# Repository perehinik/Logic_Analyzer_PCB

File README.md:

# Logic_Analizer_PCB
KiCad PCB project of Logic Analyzer

All components were soldered by hand using Zhaoxin 898DH station

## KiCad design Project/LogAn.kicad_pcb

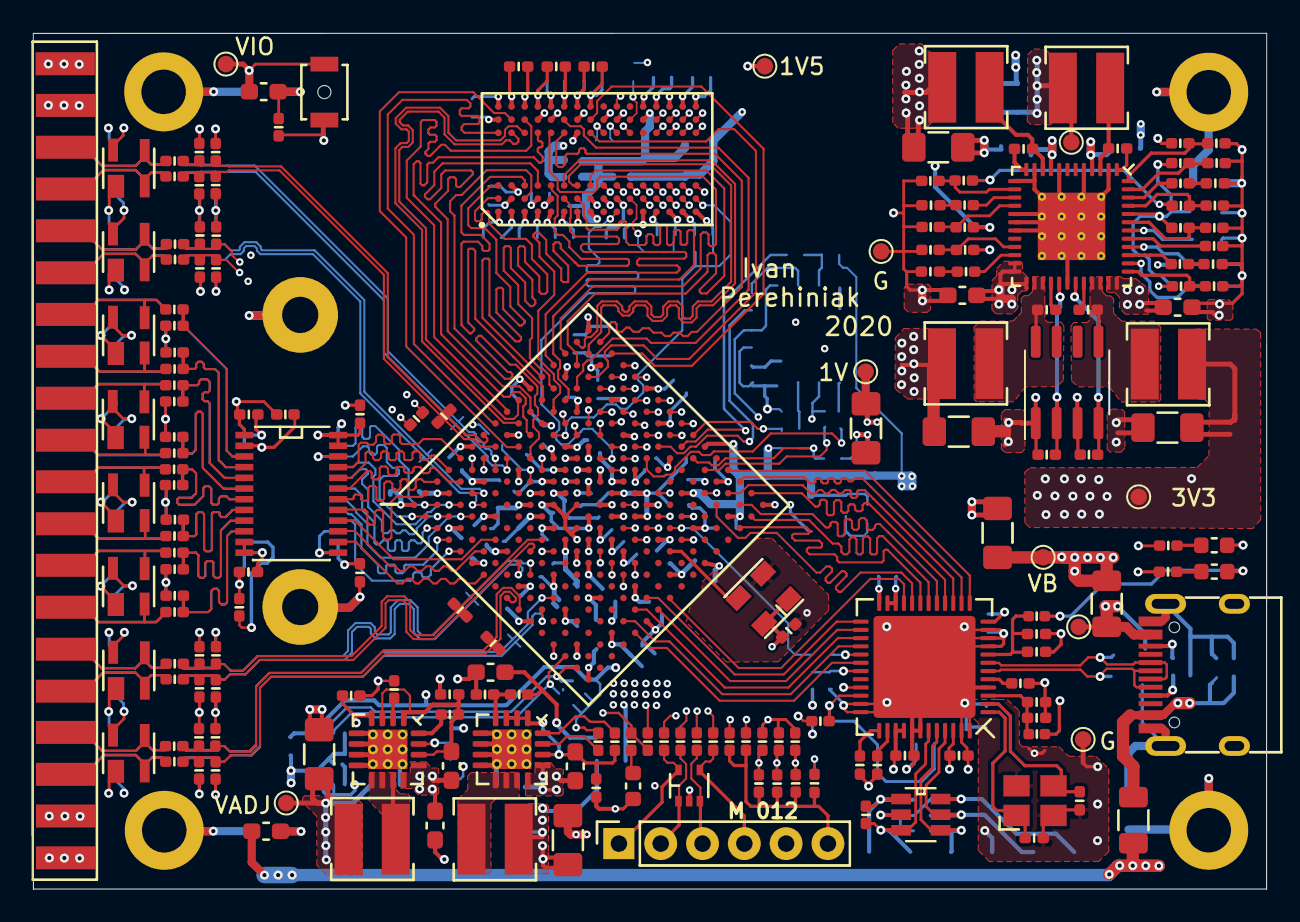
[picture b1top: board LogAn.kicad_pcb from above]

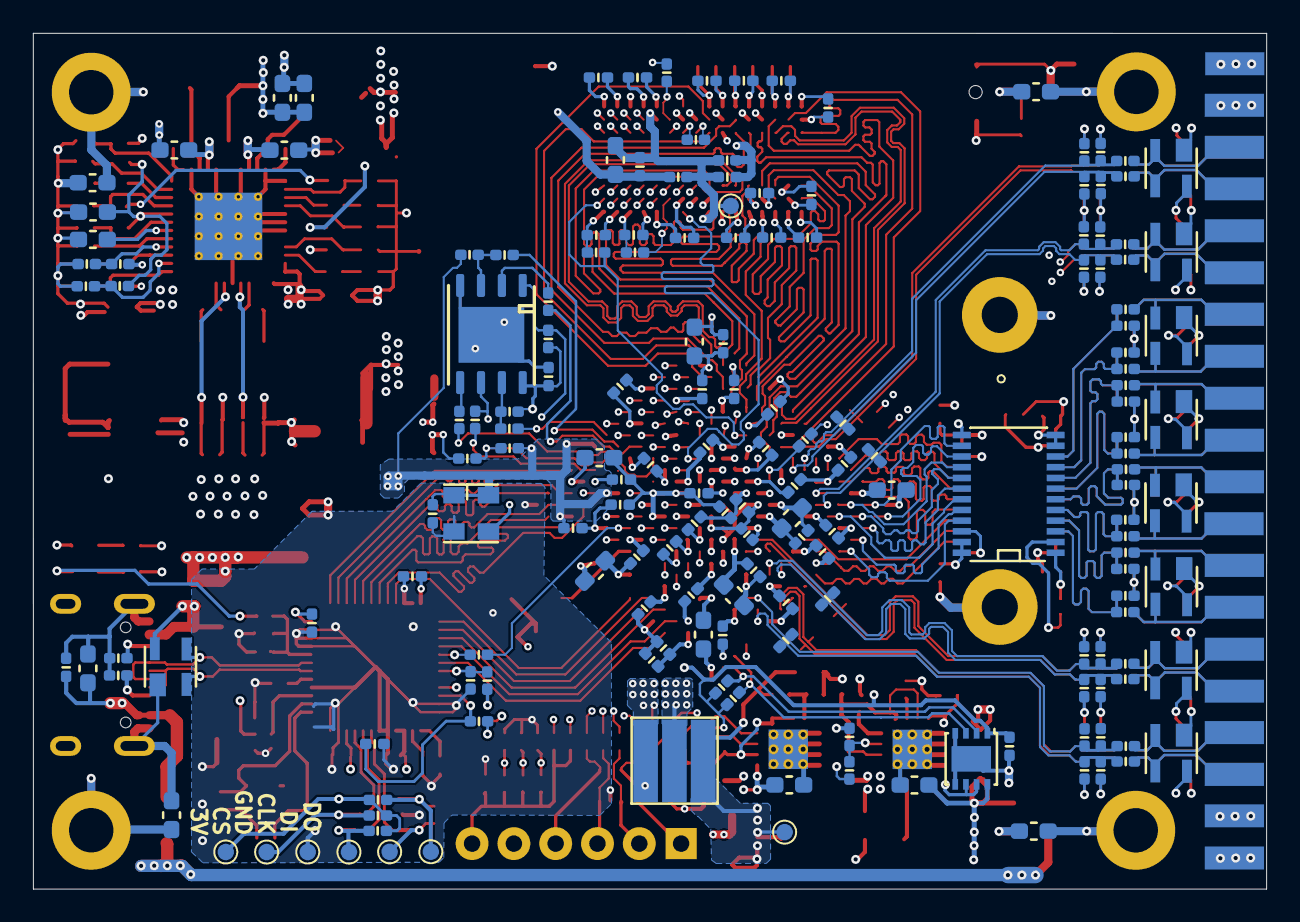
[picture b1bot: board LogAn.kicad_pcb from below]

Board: 6 copper layers, 74.9 x 52.0 mm, 366 parts (174 on the bottom side), 264 nets.

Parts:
C101, C525, C807, C808, C824, C825, C827: C_100u_1206_6V3; C_1206_3216Metric_Pad1.42x1.75mm_HandSolder
C102, C201, C401, C402, C403, C404, C521, C534, C601, C605, C606, C607, C608, C610, C611, C612, C802, C804, C809, C820, C821, C822, C823: C_100n_0402_16V; C_0402_1005Metric
C103, C503, C511, C516, C518, C535, C537, C801, C803, C805, C806: C_47u_0603_6V3; C_0603_1608Metric_Pad1.05x0.95mm_HandSolder
C104, C105, C810, C811, C812, C813: C_10u_0603_10V; C_0603_1608Metric_Pad1.05x0.95mm_HandSolder
C301, C302, C303, C304, C305, C306, C307, C308, C309, C310, C311, C312, C313, C314, C315, C316, C317: C_47n_0402_16V; C_0402_1005Metric
C318, C814, C819: C_1u_0603_10V; C_0603_1608Metric_Pad1.05x0.95mm_HandSolder
C319, C320, C506, C604, C701, C702: C_10n_0402_16V; C_0402_1005Metric
C501, C502, C505, C507, C509, C517, C519, C520, C522, C523, C524, C526, C527, C529: C_470n_0402_6V3; C_0402_1005Metric
C504, C508, C510, C512, C513, C515, C528, C530, C531, C532, C533, C536, C609, C613: C_4u7_0402_6V3; C_0402_1005Metric
C514: C_470n_0603_16V; C_0603_1608Metric_Pad1.05x0.95mm_HandSolder
C602, C603: C_27p_0402_16V; C_0402_1005Metric
C815: C_2n7_0402_10V; C_0402_1005Metric
C816: C_5n6_0402_10V; C_0402_1005Metric
C817, C818: C_1n8_0402_10V; C_0402_1005Metric
C826, C828: C_22u_0603_6V3; C_0603_1608Metric_Pad1.05x0.95mm_HandSolder
D201: D_NSQA6V8AW5T2_SOT23; SOT-353_SC-70-5
F101, F102: F_Polyfuse_1A_1206; Fuse_1206_3216Metric
FB501, FB502, FB601, FB602: FB_600R_100MHz_0,5A; L_0402_1005Metric
IC101, IC403, IC404, IC405, IC406, IC407, IC408, IC409, IC410, IC411, IC412, IC413, IC414, IC415, IC416, IC417, IC418: IC_TPD2E001DZD; SOT-143(R_PDSO-G4)
IC201: IC_XC7A15T_FTG256; Xilinx_FTG256
IC202: IC_S25FL064L-ABNFI040_WSON8; WSON-8-1EP_6x5mm_P1.27mm_EP3.4x4mmj
IC301: IC_MT41K128M16JT-125K_FBGA96; FBGA96_C80P9X16_800X1400X120
IC401, IC402: IC_SN74AVC8T245PW_TSSOP_24; TSSOP-24_4.4x7.8mm_P0.65mm
IC601: IC_93LC56BT-1OT; SOT-23-6
IC602: IC_FT232H_QFN48; QFN-48-1EP_8x8mm_P0.5mm_EP6.2x6.2mm
IC701, IC702: IC_ASEM1_100MHZ_3.2_2.5; OSC_SMD_3225-4Pin_3.2x2.5mm
IC801, IC802: IC_ADP2164; LFCSP-16-1EP_4x4mm_P0.65mm_EP2.4x2.4mm_ThermalVias
IC803: IC_MAX5417; DFN-8-1EP_3x3mm_P0.65mm_EP1.55x2.4mm
IC804: IC_ADP5052_LFCSP48; LFCSP-48-1EP_7x7mm_P0.5mm_EP4.1x4.1mm_ThermalVias
J101: J_USB_C_Receptacle_USB2.0; USB_C_Receptacle_HRO_TYPE-C-31-M-12
J102: J_Conn_01x06_Male_2_54; PinSocket_1x06_P2.54mm_Vertical
J103, J104, J105, J106: MH_M2_5; MH_2_5_mm
J107: GND_PCB
J108: J_Conn_02x20_2.5_M_SMD_HOR; PinSocket_2x20_P2.54mm_SMD_HOR
JP101: Jumper_NC_Dual; SolderJumper_6_2
L801, L802: L_1u_4x4mm; L_4.3x4.3_H3
L803: L_2u2_4x4mm; L_4.3x4.3_H3
L804: L_3u3_4x4mm; L_4.3x4.3_H3
L805, L806: L_4u7_4x4mm; L_4.3x4.3_H3
LD201, LD601, LD701: LED_Green_0603; LED_0603_1608Metric
Q801: Q_FDS6890A_SOIC8; SOIC-8_3.9x4.9mm_P1.27mm
R101, R102: R_5k1_0402_1%; R_0402_1005Metric
R103, R104, R105, R106: R_1M_0603_5%; R_0603_1608Metric_Pad1.05x0.95mm_HandSolder
R201, R202, R203, R204, R205, R206, R212, R213, R304, R601, R609, R701, R702: R_1k_0402_5%; R_0402_1005Metric
R207, R208, R209, R210, R215, R216, R217, R218, R220, R451, R452, R453, R454, R487, R488, R489, R490: R_100r_0402_5%; R_0402_1005Metric
R211, R221, R222, R223, R306, R610, R817, R823: R_4k7_0402_5%; R_0402_1005Metric
R214: R_330r_0402_5%; R_0402_1005Metric
R219: R_49r9_0402_1%; R_0402_1005Metric
R224, R225: R_1k8_0402_5%; R_0402_1005Metric
R301: R_80r6_0402_1%; R_0402_1005Metric
R302, R303: R_1k_0402_1%; R_0402_1005Metric
R305, R455, R456, R457, R458, R459, R460, R461, R462, R463, R464, R465, R466, R467, R468, R469, R470, R471, R472, R473, R474, R475, R476, R477, R478, R479, R480, R481, R482, R483, R484, R485, R486: R_240r_0402_1%; R_0402_1005Metric
R401, R402, R403, R404, R405, R406, R407, R408, R409, R410, R411, R412, R413, R414, R415, R416, R419, R420, R421, R422, R423, R424, R425, R426, R427, R428, R429, R430, R431, R432, R433, R434, R435, R436, R437, R438, R439, R440, R441, R442, R443, R444, R445, R446, R447, R448, R449, R450: R_200k_0402_5%; R_0402_1005Metric
R417, R418, R602, R603, R605, R606, R611, R802, R804, R805, R806, R808: R_10k_0402_5%; R_0402_1005Metric
R604: R_2k_0402_5%; R_0402_1005Metric
R607, R840: R_12k_0402_1%; R_0402_1005Metric
R608: R_27k_0402_5%; R_0402_1005Metric
R801, R803: R_10r_0603_5%; R_0603_1608Metric_Pad1.05x0.95mm_HandSolder
R807: R_82k_0402_5%; R_0402_1005Metric
R809, R811, R827: R_15k_0402_1%; R_0402_1005Metric
R810: R_4k7_0402_1%; R_0402_1005Metric
R812: R_4k64_0402_1%; R_0402_1005Metric
R813, R816: R_9k53_0402_1%; R_0402_1005Metric
R814: R_270r_0402_1%; R_0402_1005Metric
R815: R_402k_0402_1%; R_0402_1005Metric
R818, R820, R822: R_10k_0402_1%; R_0402_1005Metric
R819, R828, R835: R_0_0402; R_0402_1005Metric
R821: R_301k_0402_1%; R_0402_1005Metric
R824: R_56k2_0402_1%; R_0402_1005Metric
R825: R_7k15_0402_1%; R_0402_1005Metric
R826: R_9k31_0402_1%; R_0402_1005Metric
R829, R830: R_47k_0402_5%; R_0402_1005Metric
R831, R836: R_31k6_0402_1%; R_0402_1005Metric
R832: R_7k68_0402_1%; R_0402_1005Metric
R833: R_12k7_0402_1%; R_0402_1005Metric
R834: R_10k5_0402_1%; R_0402_1005Metric
R837, R839: R_10k2_0402_1%; R_0402_1005Metric
R838: R_41k2_0402_1%; R_0402_1005Metric
SW701: SW_B3U-1000PM-B; SW_SPST_B3U-1000P-B
TP101, TP102, TP301, TP401, TP601, TP602, TP603, TP604, TP605, TP606, TP801, TP802, TP803, TP804, TP805, TP806, TP807, TP808: TestPoint; TestPoint_Pad_D1.0mm
X601: X_Crystal_12MHz_3_2x2_5; Crystal_SMD_3225-4Pin_3.2x2.5mm

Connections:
/Comunication/FT_CONF0: IC201.T8, IC602.21
/Comunication/FT_CONF1: IC201.R7, IC602.25
/Comunication/FT_CONF2: IC201.T7, IC602.26
/Comunication/FT_CONF3: IC201.R6, IC602.27
/Comunication/FT_CONF4: IC201.R5, IC602.28
/Comunication/FT_CONF5: IC201.N11, R608.2
/Comunication/FT_CONF6: IC201.T5, IC602.30
/Comunication/FT_DATA0: IC201.N16, IC602.13
/Comunication/FT_DATA1: IC201.P16, IC602.14
/Comunication/FT_DATA2: IC201.P15, IC602.15
/Comunication/FT_DATA3: IC201.R16, IC602.16
/Comunication/FT_DATA4: IC201.R15, IC602.17
/Comunication/FT_DATA5: IC201.T15, IC602.18
/Comunication/FT_DATA6: IC201.T14, IC602.19
/Comunication/FT_DATA7: IC201.P14, IC602.20
/Comunication/USB_DM: IC101.2, IC602.6, J101.A7, J101.B7
/Comunication/USB_DP: IC101.3, IC602.7, J101.A6, J101.B6
/Comunication/USB_RST: IC201.P11, R601.1
/Comunication/VBUS: C101.1, C810.1, C811.1, C812.1, C813.1, F102.2, IC804.4, IC804.9, IC804.23, IC804.24, IC804.25, IC804.35, IC804.36, R610.1, TP803.1
/DDR3/DDR1V5: C301.1, C302.1, C303.1, C304.2, C305.2, C306.1, C307.1, C308.1, C309.1, C310.1, C311.1, C312.2, C313.2, C314.2, C315.1, C316.1, C317.1, C320.1, C520.1, C523.1, C526.1, C529.1, C533.1, C536.1, C537.1, C827.1, IC201.A16, IC201.B13, IC201.C10, IC201.E14, IC201.H15, IC201.J12, IC301.A1, IC301.A8, IC301.B2, IC301.C1, IC301.C9, IC301.D2, IC301.D9, IC301.E9, IC301.F1, IC301.G7, IC301.H2, IC301.H9, IC301.K2, IC301.K8, IC301.N1, IC301.N9, IC301.R1, IC301.R9, L806.2, R302.2, R812.1, R834.1, TP807.1
/DDR3/DDR3_A0: IC201.J16, IC301.N3
/DDR3/DDR3_A1: IC201.F13, IC301.P7
/DDR3/DDR3_A2: IC201.J15, IC301.P3
/DDR3/DDR3_A3: IC201.F15, IC301.N2
/DDR3/DDR3_A4: IC201.E12, IC301.P8
/DDR3/DDR3_A5: IC201.G15, IC301.P2
/DDR3/DDR3_A6: IC201.H11, IC301.R8
/DDR3/DDR3_A7: IC201.G16, IC301.R2
/DDR3/DDR3_A8: IC201.G12, IC301.T8
/DDR3/DDR3_A9: IC201.H16, IC301.R3
/DDR3/DDR3_A10: IC201.D11, IC301.L7
/DDR3/DDR3_A11: IC201.H13, IC301.R7
/DDR3/DDR3_A12: IC201.E13, IC301.N7
/DDR3/DDR3_A13: IC201.H14, IC301.T3
/DDR3/DDR3_A14: IC201.H12, IC301.T7
/DDR3/DDR3_BA0: IC201.D16, IC301.M3
/DDR3/DDR3_BA1: IC201.F12, IC301.N8
/DDR3/DDR3_BA2: IC201.E16, IC301.M2
/DDR3/DDR3_CKE: IC201.E11, IC301.K9
/DDR3/DDR3_CK_N: IC201.F14, IC301.K7, R301.2
/DDR3/DDR3_CK_P: IC201.G14, IC301.J7, R301.1
/DDR3/DDR3_DM0: IC201.A14, IC301.E7
/DDR3/DDR3_DM1: IC201.B10, IC301.D3
/DDR3/DDR3_DQ0: IC201.C11, IC301.E3
/DDR3/DDR3_DQ1: IC201.B16, IC301.F7
/DDR3/DDR3_DQ2: IC201.A13, IC301.F2
/DDR3/DDR3_DQ3: IC201.C13, IC301.F8
/DDR3/DDR3_DQ4: IC201.B14, IC301.H3
/DDR3/DDR3_DQ5: IC201.C16, IC301.H8
/DDR3/DDR3_DQ6: IC201.C12, IC301.G2
/DDR3/DDR3_DQ7: IC201.C14, IC301.H7
/DDR3/DDR3_DQ8: IC201.C9, IC301.D7
/DDR3/DDR3_DQ9: IC201.B11, IC301.C3
/DDR3/DDR3_DQ10: IC201.A9, IC301.C8
/DDR3/DDR3_DQ11: IC201.D8, IC301.C2
/DDR3/DDR3_DQ12: IC201.A8, IC301.A7
/DDR3/DDR3_DQ13: IC201.B12, IC301.A2
/DDR3/DDR3_DQ14: IC201.C8, IC301.B8
/DDR3/DDR3_DQ15: IC201.A12, IC301.A3
/DDR3/DDR3_DQS0_N: IC201.A15, IC301.G3
/DDR3/DDR3_DQS0_P: IC201.B15, IC301.F3
/DDR3/DDR3_DQS1_N: IC201.A10, IC301.B7
/DDR3/DDR3_DQS1_P: IC201.B9, IC301.C7
/DDR3/DDR3_ODT: IC201.G11, IC301.K1
/DDR3/DDR3_nCAS: IC201.D14, IC301.K3
/DDR3/DDR3_nRAS: IC201.D15, IC301.J3
/DDR3/DDR3_nRST: IC201.D10, IC301.T2, R306.1
/DDR3/DDR3_nWE: IC201.E15, IC301.L3
/DDR3/DDR_VREF: C318.1, C319.1, C320.2, IC301.H1, IC301.M8, R302.1, R303.1, TP301.1
/DIO_P_0: IC403.3, J108.5, R456.2
/DIO_P_1: IC403.2, J108.7, R457.2
/DIO_P_2: IC405.2, J108.6, R458.2
/DIO_P_3: IC405.3, J108.8, R459.2
/DIO_P_4: IC407.3, J108.9, R460.2
/DIO_P_5: IC407.2, J108.11, R461.2
/DIO_P_6: IC409.2, J108.10, R462.2
/DIO_P_7: IC409.3, J108.12, R463.2
/DIO_P_8: IC411.3, J108.13, R464.2
/DIO_P_9: IC413.2, J108.14, R465.2
/DIO_P_10: IC411.2, J108.15, R466.2
/DIO_P_11: IC413.3, J108.16, R467.2
/DIO_P_12: IC415.3, J108.17, R468.2
/DIO_P_13: IC417.2, J108.18, R469.2
/DIO_P_14: IC415.2, J108.19, R470.2
/DIO_P_15: IC417.3, J108.20, R471.2
/DIO_P_16: IC418.3, J108.21, R472.2
/DIO_P_17: IC416.2, J108.22, R473.2
/DIO_P_18: IC418.2, J108.23, R474.2
/DIO_P_19: IC416.3, J108.24, R475.2
/DIO_P_20: IC414.3, J108.25, R476.2
/DIO_P_21: IC412.2, J108.26, R477.2
/DIO_P_22: IC414.2, J108.27, R478.2
/DIO_P_23: IC412.3, J108.28, R479.2
/DIO_P_24: IC410.3, J108.29, R480.2
/DIO_P_25: IC410.2, J108.31, R455.2
/DIO_P_26: IC408.2, J108.30, R481.2
/DIO_P_27: IC408.3, J108.32, R482.2
/DIO_P_28: IC406.3, J108.33, R483.2
/DIO_P_29: IC406.2, J108.35, R484.2
/DIO_P_30: IC404.2, J108.34, R485.2
/DIO_P_31: IC404.3, J108.36, R486.2
/FPGA_Bank/ADJ_EN: IC201.N1, R805.2
/FPGA_Bank/CLK_1: IC201.N14, IC701.3
/FPGA_Bank/CLK_2: IC201.P10, IC702.3
/FPGA_Bank/DIO_0: IC201.L2, R419.1, R435.2, R451.1, R456.1
/FPGA_Bank/DIO_1: IC201.L3, R420.1, R436.2, R451.2, R457.1
/FPGA_Bank/DIO_2: IC201.J1, R421.1, R437.2, R452.1, R458.1
/FPGA_Bank/DIO_3: IC201.K1, R422.1, R438.2, R452.2, R459.1
/FPGA_Bank/DIO_4: IC201.H3, R423.1, R439.2, R453.1, R460.1
/FPGA_Bank/DIO_5: IC201.J3, R424.1, R440.2, R453.2, R461.1
/FPGA_Bank/DIO_6: IC201.H4, R425.1, R441.2, R454.1, R462.1
/FPGA_Bank/DIO_7: IC201.H5, R426.1, R442.2, R454.2, R463.1
/FPGA_Bank/DIO_8: IC201.E1, IC402.21
/FPGA_Bank/DIO_9: IC201.G1, IC401.14
/FPGA_Bank/DIO_10: IC201.D1, IC402.20
/FPGA_Bank/DIO_11: IC201.F2, IC401.15
/FPGA_Bank/DIO_12: IC201.D3, IC402.19
/FPGA_Bank/DIO_13: IC201.F3, IC401.16
/FPGA_Bank/DIO_14: IC201.C1, IC402.18
/FPGA_Bank/DIO_15: IC201.A2, IC401.17
/FPGA_Bank/DIO_16: IC201.C2, IC402.17
/FPGA_Bank/DIO_17: IC201.A3, IC401.18
/FPGA_Bank/DIO_18: IC201.C3, IC402.16
/FPGA_Bank/DIO_19: IC201.B4, IC401.19
/FPGA_Bank/DIO_20: IC201.B1, IC402.15
/FPGA_Bank/DIO_21: IC201.A4, IC401.20
/FPGA_Bank/DIO_22: IC201.B2, IC402.14
/FPGA_Bank/DIO_23: IC201.A5, IC401.21
/FPGA_Bank/DIO_24: IC201.D4, R427.1, R443.2, R480.1, R487.1
/FPGA_Bank/DIO_25: IC201.C4, R428.1, R444.2, R455.1, R487.2
/FPGA_Bank/DIO_26: IC201.B6, R429.1, R445.2, R481.1, R488.1
/FPGA_Bank/DIO_27: IC201.B5, R430.1, R446.2, R482.1, R488.2
/FPGA_Bank/DIO_28: IC201.C7, R431.1, R447.2, R483.1, R489.1
/FPGA_Bank/DIO_29: IC201.C6, R432.1, R448.2, R484.1, R489.2
/FPGA_Bank/DIO_30: IC201.B7, R433.1, R449.2, R485.1, R490.1
/FPGA_Bank/DIO_31: IC201.A7, R434.1, R450.2, R486.1, R490.2
/FPGA_Bank/LED_FPGA: IC201.N12, R701.1
/FPGA_Bank/TRIM_SCL: IC201.R1, IC803.2, R817.1
/FPGA_Bank/TRIM_SDA: IC201.P1, IC803.3, R823.1
/FPGA_Bank/USER_BTN: IC201.J5, R702.2, SW701.1
/FPGA_Cornfig/ADCGND: C506.2, FB502.2, IC201.G7, IC201.H7, IC201.H8, IC201.J7, IC201.J8
/FPGA_Cornfig/TCK: D201.4, J102.4, R207.1
/FPGA_Cornfig/TDI_FPGA: D201.1, J102.2, R210.1
/FPGA_Cornfig/TDO_FPGA: D201.3, J102.3, R209.1
/FPGA_Cornfig/TMS: D201.5, J102.1, R208.1
/FPGA_Supply/ADCVCC: C502.1, C506.1, FB501.2, IC201.G8
/FPGA_Supply/VCC1V0: C511.1, C514.1, C519.1, C522.1, C525.1, C528.1, C531.1, C534.1, C824.1, IC201.E10, IC201.F7, IC201.F9, IC201.F11, IC201.G6, IC201.H9, IC201.J6, IC201.K9, IC201.L8, L804.2, R814.1, R832.1, TP805.1
/FPGA_Supply/VCC1V8: C501.1, C503.1, C504.1, C508.1, C517.1, C826.1, C828.1, FB501.1, IC201.F8, IC201.G10, IC201.J10, IC201.K11, IC201.L10, L805.2, R816.1, R833.1, TP806.1
/GND: C101.2, C102.2, C103.2, C104.2, C105.1, C201.2, C301.2, C302.2, C303.2, C304.1, C305.1, C306.2, C307.2, C308.2, C309.2, C310.2, C311.2, C312.1, C313.1, C314.1, C315.2, C316.2, C317.2, C318.2, C319.2, C401.2, C402.2, C403.2, C404.2, C501.2, C502.2, C503.2, C504.2, C505.2, C507.2, C508.2, C509.2, C510.2, C511.2, C512.2, C513.2, C514.2, C515.2, C516.2, C517.2, C518.2, C519.2, C520.2, C521.2, C522.2, C523.2, C524.2, C525.2, C526.2, C527.2, C528.2, C529.2, C530.2, C531.2, C532.2, C533.2, C534.2, C535.2, C536.2, C537.2, C601.2, C602.2, C603.1, C604.2, C605.2, C606.2, C607.2, C608.2, C609.2, C610.2, C611.2, C612.2, C613.2, C701.2, C702.2, C801.2, C802.2, C803.2, C804.2, C805.2, C806.2, C807.2, C808.2, C809.2, C810.2, C811.2, C812.2, C813.2, C814.1, C815.1, C816.1, C817.1, C818.1, C819.1, C824.2, C825.2, C826.2, C827.2, C828.2, D201.2, FB502.1, IC101.1, IC201.A1, IC201.A11, IC201.B8, IC201.C5, IC201.C15, IC201.D2, IC201.D12, IC201.E9, IC201.F6, IC201.F10, IC201.F16, IC201.G3, IC201.G9, IC201.G13, IC201.H6, IC201.J9, IC201.J11, IC201.K4, IC201.K6, IC201.K7, IC201.K8, IC201.K14, IC201.L1, IC201.L11, IC201.M8, IC201.N5, IC201.N15, IC201.P2, IC201.P12, IC201.R9, IC201.T6, IC201.T16, IC202.4, IC202.9, IC301.A9, IC301.B1, IC301.B3, IC301.B9, IC301.D1, IC301.D8, IC301.E1, IC301.E2, IC301.E8, IC301.F9, IC301.G1, IC301.G8, IC301.G9, IC301.J2, IC301.J8, IC301.M1, IC301.M9, IC301.P1, IC301.P9, IC301.T1, IC301.T9, IC401.11, IC401.12, IC401.13, IC401.22, IC402.11, IC402.12, IC402.13, IC402.22, IC403.1, IC404.1, IC405.1, IC406.1, IC407.1, IC408.1, IC409.1, IC410.1, IC411.1, IC412.1, IC413.1, IC414.1, IC415.1, IC416.1, IC417.1, IC418.1, IC601.2, IC602.4, IC602.9, IC602.10, IC602.11, IC602.22, IC602.23, IC602.35, IC602.36, IC602.41, IC602.42, IC602.47, IC602.48, IC602.49, IC701.2, IC702.2, IC801.5, IC801.6, IC801.7, IC801.8, IC801.17, IC802.5, IC802.6, IC802.7, IC802.8, IC802.17, IC803.4, IC803.5, IC803.9, IC804.2, IC804.5, IC804.8, IC804.11, IC804.13, IC804.17, IC804.18, IC804.19, IC804.30, IC804.49, J101.A1, J101.A12, J101.B1, J101.B12, J101.S1, J102.5, J107.1, J108.3, J108.4, J108.37, J108.38, LD201.1, LD701.1, Q801.1, Q801.3, R101.2, R102.2, R103.2, R104.2, R105.2, R106.2, R201.2, R202.2, R203.2, R213.2, R303.2, R304.2, R305.1, R306.2, R401.2, R402.2, R403.2, R404.2, R405.2, R406.2, R407.2, R408.2, R409.2, R410.2, R411.2, R412.2, R413.2, R414.2, R415.2, R416.2, R419.2, R420.2, R421.2, R422.2, R423.2, R424.2, R425.2, R426.2, R427.2, R428.2, R429.2, R430.2, R431.2, R432.2, R433.2, R434.2, R607.2, R611.2, R702.1, R807.2, R810.2, R811.2, R818.1, R819.2, R820.2, R821.2, R822.2, R829.2, R830.2, R835.2, R836.2, R837.2, R838.2, R839.2, R840.2, TP102.1, TP602.1, TP804.1, X601.2, X601.4
/IO_Protection/DIO_8_b: IC402.3, R401.1, R464.1
/IO_Protection/DIO_9_b: IC401.10, R402.1, R465.1
/IO_Protection/DIO_10_b: IC402.4, R403.1, R466.1
/IO_Protection/DIO_11_b: IC401.9, R404.1, R467.1
/IO_Protection/DIO_12_b: IC402.5, R405.1, R468.1
/IO_Protection/DIO_13_b: IC401.8, R406.1, R469.1
/IO_Protection/DIO_14_b: IC402.6, R407.1, R470.1
/IO_Protection/DIO_15_b: IC401.7, R408.1, R471.1
/IO_Protection/DIO_16_b: IC402.7, R409.1, R472.1
/IO_Protection/DIO_17_b: IC401.6, R410.1, R473.1
/IO_Protection/DIO_18_b: IC402.8, R411.1, R474.1
/IO_Protection/DIO_19_b: IC401.5, R412.1, R475.1
/IO_Protection/DIO_20_b: IC402.9, R413.1, R476.1
/IO_Protection/DIO_21_b: IC401.4, R414.1, R477.1
/IO_Protection/DIO_22_b: IC402.10, R415.1, R478.1
/IO_Protection/DIO_23_b: IC401.3, R416.1, R479.1
/IO_Protection/VCCADJ: C401.1, C402.1, C805.1, C807.1, IC401.1, IC402.1, IC411.4, IC412.4, IC413.4, IC414.4, IC415.4, IC416.4, IC417.4, IC418.4, IC803.8, L802.2, R417.1, R418.1, TP802.1
/Power_supply/VREG: C814.2, IC804.44, R813.1, R815.1, R828.1
/VCC5V0_2: C104.1, C801.1, C803.1, F101.2, IC801.12, IC801.13, IC802.12, IC802.13, J108.1, J108.2, R801.2, R803.2
/VCC_2V5: C806.1, C808.1, JP101.1, L801.2, R809.1, TP801.1
/VCC_3V3: C201.1, C505.1, C507.1, C509.1, C510.1, C512.1, C513.1, C515.1, C516.1, C518.1, C521.1, C601.1, C608.1, C610.1, C612.1, C701.1, C702.1, C809.1, C825.1, FB601.1, FB602.1, IC201.L6, IC201.L16, IC201.M3, IC201.M13, IC201.N10, IC201.P7, IC201.R4, IC201.R14, IC201.T1, IC201.T11, IC202.8, IC601.6, IC602.12, IC602.24, IC602.39, IC602.40, IC602.46, IC701.1, IC701.4, IC702.1, IC702.4, IC803.1, J102.6, JP101.3, L803.2, LD601.2, R204.1, R205.1, R206.1, R211.1, R212.1, R214.1, R221.1, R222.1, R223.1, R224.1, R225.1, R602.1, R603.1, R605.1, R606.1, R804.1, R817.2, R823.2, R831.1, TP601.1, TP808.1
/VCC_IO: C105.2, C403.1, C404.1, C524.1, C527.1, C530.1, C532.1, C535.1, IC201.A6, IC201.B3, IC201.D7, IC201.E4, IC201.F1, IC201.J2, IC401.23, IC401.24, IC402.23, IC402.24, IC403.4, IC404.4, IC405.4, IC406.4, IC407.4, IC408.4, IC409.4, IC410.4, J108.39, J108.40, JP101.2, R435.1, R436.1, R437.1, R438.1, R439.1, R440.1, R441.1, R442.1, R443.1, R444.1, R445.1, R446.1, R447.1, R448.1, R449.1, R450.1, SW701.2, TP401.1
unnamed: C102.1, C103.1, F101.1, F102.1, IC101.4, J101.A4, J101.A9, J101.B4, J101.B9, TP101.1
unnamed: C602.1, IC602.1, X601.1
unnamed: C603.2, IC602.2, X601.3
unnamed: C604.1, IC602.34, R601.2, R602.2
unnamed: C605.1, IC602.38
unnamed: C606.1, IC602.37
unnamed: C607.1, C609.1, FB602.2, IC602.3
unnamed: C611.1, C613.1, FB601.2, IC602.8
unnamed: C802.1, IC801.1, IC801.2, IC801.3, IC801.14, R801.1, R802.1
unnamed: C804.1, IC802.1, IC802.3, IC802.14, R803.1, R806.1
unnamed: C815.2, R824.1
unnamed: C816.2, R825.1
unnamed: C817.2, R826.1
unnamed: C818.2, R827.1
unnamed: C819.2, IC804.42
unnamed: C820.1, IC804.1
unnamed: C820.2, IC804.3, L805.1
unnamed: C821.1, IC804.12
unnamed: C821.2, IC804.10, L806.1
unnamed: C822.1, IC804.32
unnamed: C822.2, IC804.33, IC804.34, L803.1, Q801.7, Q801.8
unnamed: C823.1, IC804.28
unnamed: C823.2, IC804.26, IC804.27, L804.1, Q801.5, Q801.6
unnamed: IC201.E7, R211.2
unnamed: IC201.E8, IC202.6, R219.2
unnamed: IC201.H10, R214.2, R215.1
unnamed: IC201.J13, R216.1
unnamed: IC201.J14, R217.1
unnamed: IC201.K10, R222.2
unnamed: IC201.K15, R218.1
unnamed: IC201.K16, R220.1
unnamed: IC201.L7, R207.2
unnamed: IC201.L9, R221.2
unnamed: IC201.L12, IC202.1, R223.2
unnamed: IC201.L15, R212.2, R213.1
unnamed: IC201.M7, R208.2
unnamed: IC201.M9, R203.1, R204.2
unnamed: IC201.M10, R202.1, R205.2
unnamed: IC201.M11, R201.1, R206.2
unnamed: IC201.M15, R219.1
unnamed: IC201.N7, R210.2
unnamed: IC201.N8, R209.2
unnamed: IC202.2, R217.2
unnamed: IC202.3, R218.2, R225.2
unnamed: IC202.5, R216.2
unnamed: IC202.7, R220.2, R224.2
unnamed: IC301.L2, R304.1
unnamed: IC301.L8, R305.2
unnamed: IC401.2, R418.2
unnamed: IC402.2, R417.2
unnamed: IC601.1, R603.2, R604.1, TP603.1
unnamed: IC601.3, IC602.43, R604.2, TP604.1
unnamed: IC601.4, IC602.44, R605.2, TP605.1
unnamed: IC601.5, IC602.45, R606.2, TP606.1
unnamed: IC602.5, R607.1
unnamed: IC602.29, R608.1
unnamed: IC602.31, R610.2, R611.1
unnamed: IC602.33, R609.1
unnamed: IC801.4, R809.2, R810.1
unnamed: IC801.9, IC801.10, IC801.11, L801.1
unnamed: IC801.15, R804.2
unnamed: IC801.16, R802.2
unnamed: IC802.2, R807.1
unnamed: IC802.4, IC803.6, IC803.7, R811.1
unnamed: IC802.9, IC802.10, IC802.11, L802.1
unnamed: IC802.15, R805.1, R808.1
unnamed: IC802.16, R806.2
unnamed: IC804.14, R816.2, R822.1
unnamed: IC804.15, R827.2
unnamed: IC804.16, R834.2, R840.1
unnamed: IC804.21, R832.2, R838.1
unnamed: IC804.22, R825.2
unnamed: IC804.29, Q801.4, R830.1
unnamed: IC804.31, Q801.2, R829.1
unnamed: IC804.37, R812.2, R818.2
unnamed: IC804.38, R813.2, R819.1
unnamed: IC804.39, R824.2
unnamed: IC804.40, R831.2, R837.1
unnamed: IC804.41, R836.1
unnamed: IC804.43, R828.2, R835.1
unnamed: IC804.45, R833.2, R839.1
unnamed: IC804.46, R826.2
unnamed: IC804.47, R815.2, R821.1
unnamed: IC804.48, R814.2, R820.1
unnamed: J101.A5, R102.1
unnamed: J101.B5, R101.1
unnamed: J103.1, R103.1
unnamed: J104.1, R104.1
unnamed: J105.1, R105.1
unnamed: J106.1, R106.1
unnamed: LD201.2, R215.2
unnamed: LD601.1, R609.2
unnamed: LD701.2, R701.2

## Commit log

2021-01-03 Full PCB project
